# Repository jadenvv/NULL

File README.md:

# NULL: A Development Board for Pentesters
NULL is a ESP32-S3 based PCB board with capabilities of infrared emulation, RFID transceiving, ARP-spoofing on WiFi Networks, and LoRa Puck capabilities. Developed with a mixture of the ESP-IDF development environment 
## What was the motivation for NULL? 
The origins of the development of NULL really came out of the intrigue of the flipper zero. I wanted to create a cheaper alternative to what seemed like an amazing development board for pentesting enthuastist. And, not only did I create a cheaper alternative for myself, but added an additional feature of a LoRA puck boosting the overall usefullness of the board.
## Images of Schematic & Wiring 

4 Layer Board with the layout
<- SIGNAL  ->
<- GND  ->
<- POWER  ->
<- SIGNAL/GND  ->

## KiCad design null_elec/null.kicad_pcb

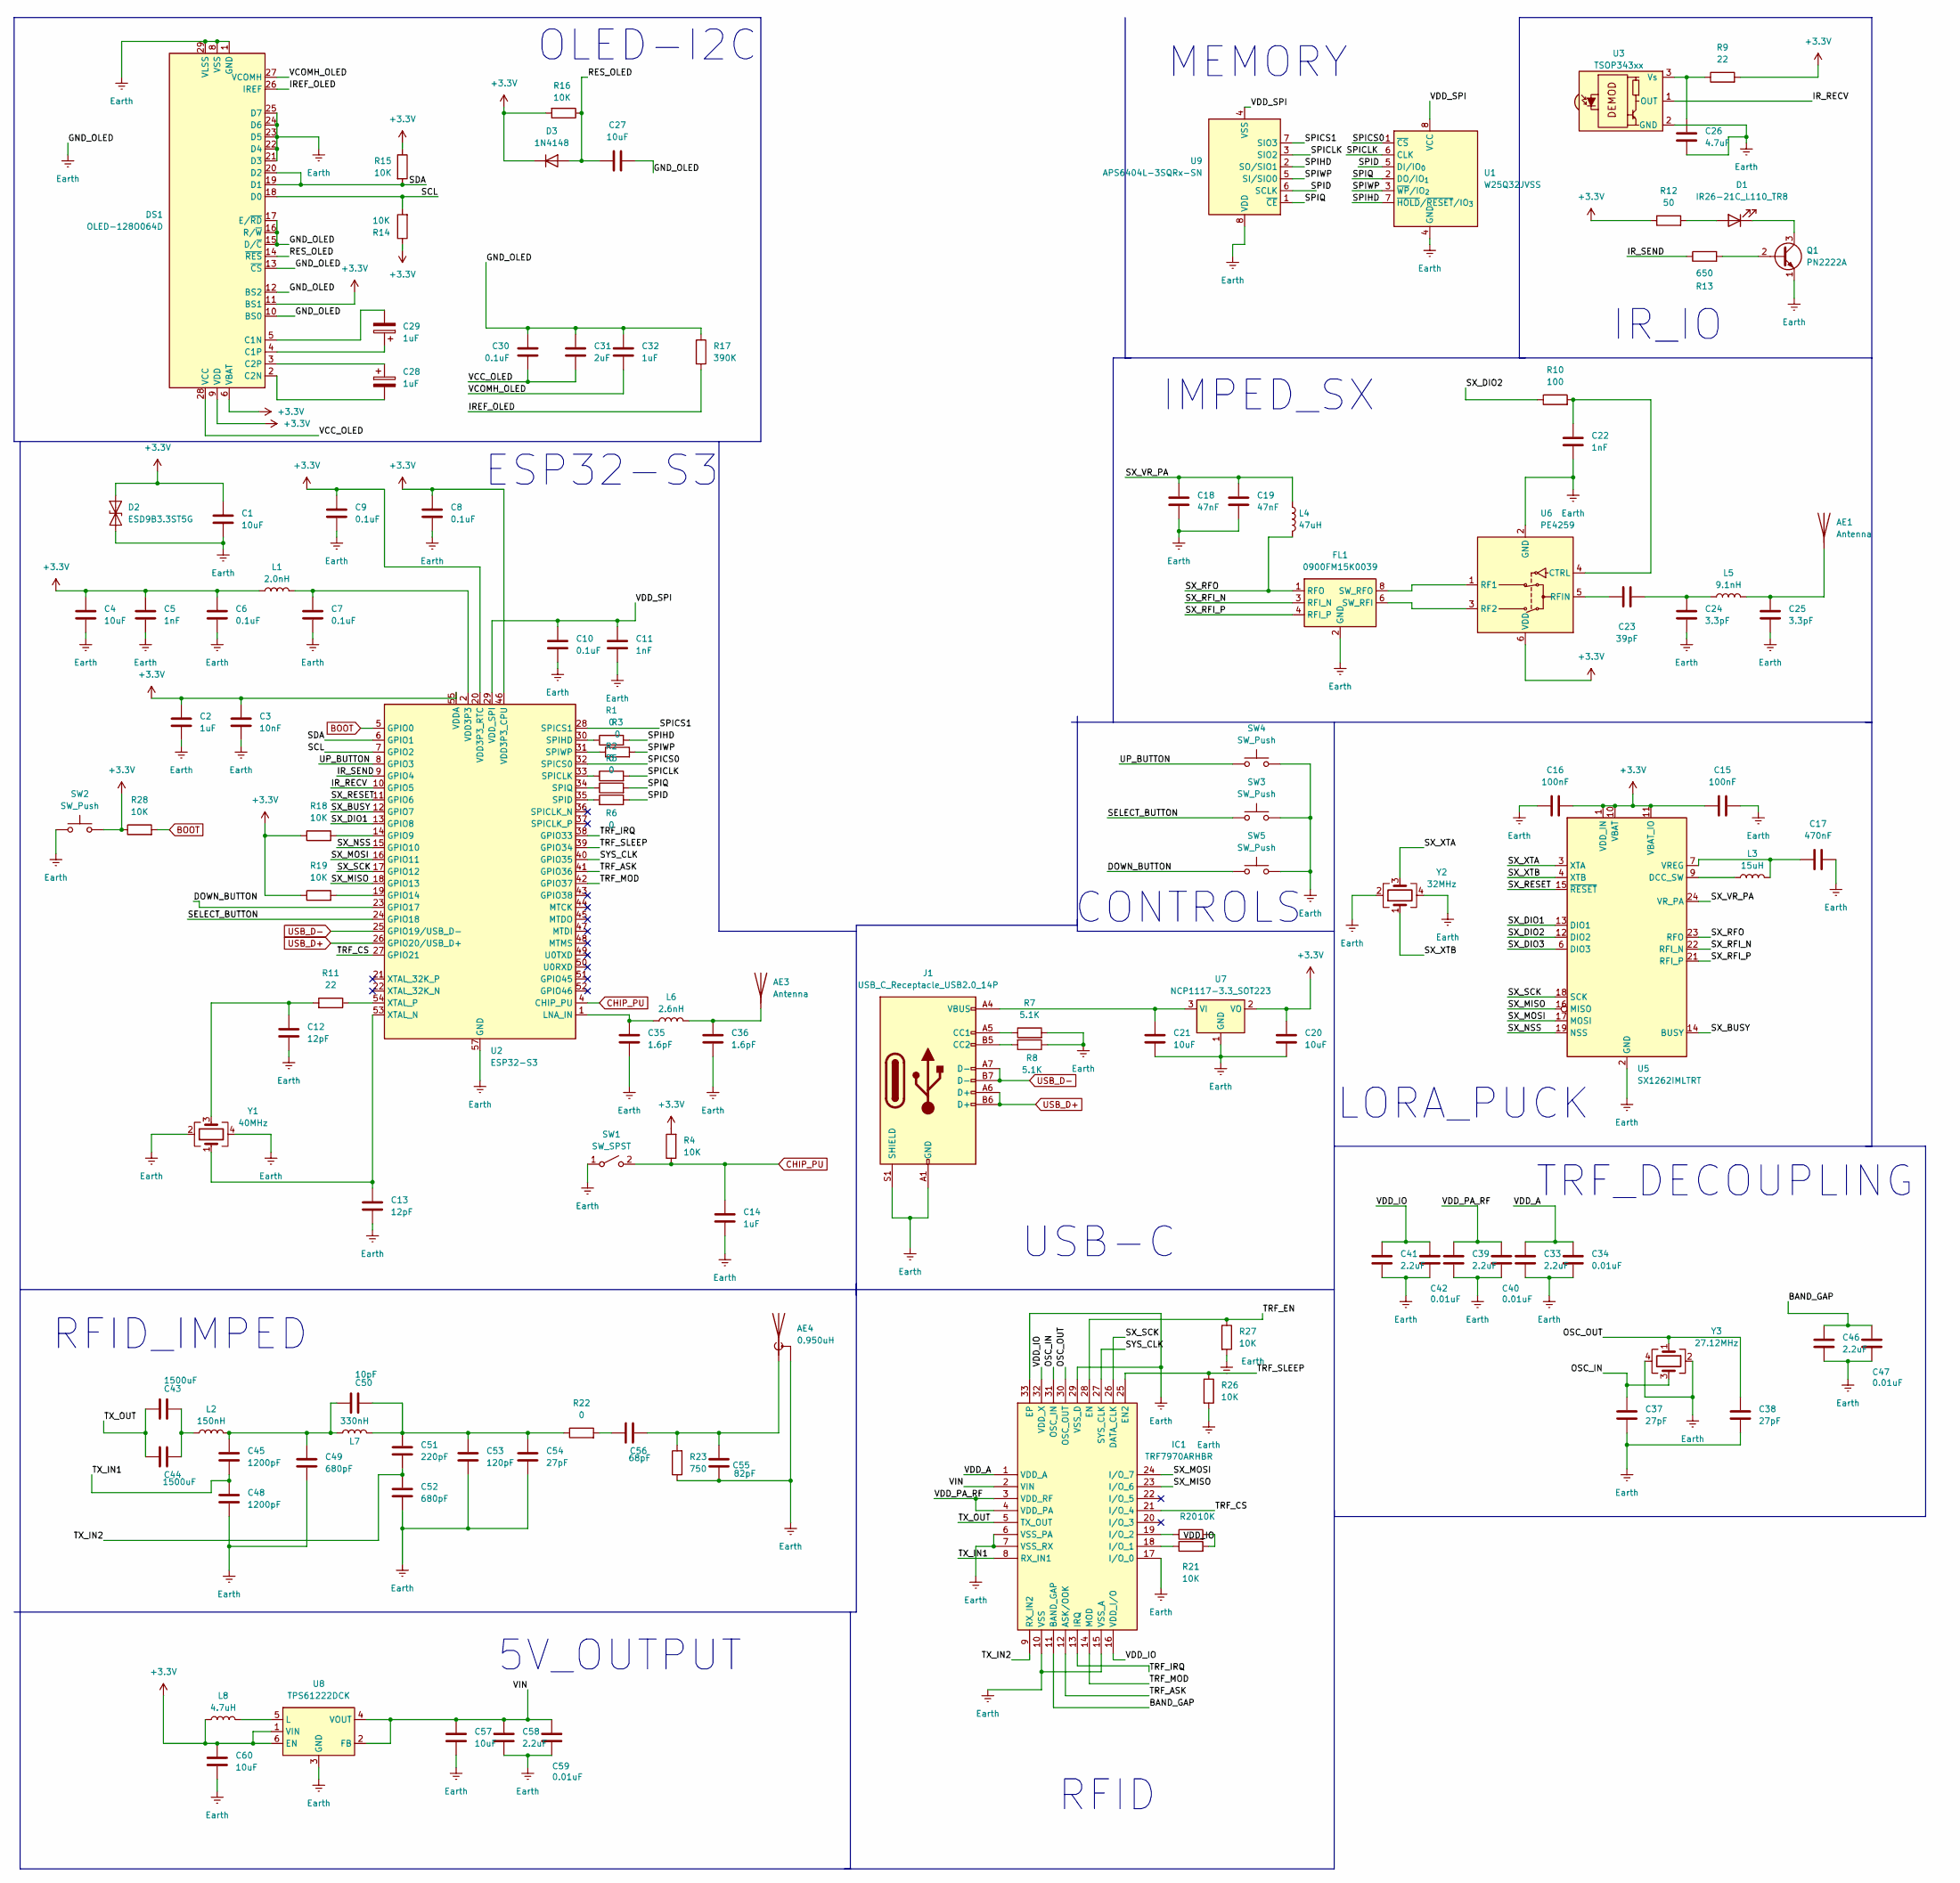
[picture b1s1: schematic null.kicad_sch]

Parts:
AE1: Antenna; PinSocket_1x01_P2.54mm_Vertical
AE3: Antenna; Molex_47948-0001_2.4Ghz
AE4: 0.950uH; Coilcraft_MA5532-AE_RFID
C1, C4, C20, C21, C60: 10uF; C_0805_2012Metric
C2, C14, C28, C29, C32: 1uF; C_0402_1005Metric
C3: 10nF; C_0805_2012Metric
C5, C11, C22: 1nF; C_0402_1005Metric
C6, C7, C8, C9, C10, C30: 0.1uF; C_0402_1005Metric
C12, C13: 12pF; C_0402_1005Metric
C15, C16: 100nF; C_0402_1005Metric
C17: 470nF; C_0402_1005Metric
C18, C19: 47nF; C_0402_1005Metric
C23: 39pF; C_0402_1005Metric
C24, C25: 3.3pF; C_0402_1005Metric
C26: 4.7uF; C_0402_1005Metric
C27, C57: 10uF; C_0402_1005Metric
C31: 2uF; C_0402_1005Metric
C33, C39, C41, C46, C58: 2.2uF; C_0402_1005Metric
C34, C40, C42, C47, C59: 0.01uF; C_0402_1005Metric
C35, C36: 1.6pF; C_0402_1005Metric
C37, C38, C54: 27pF; C_0402_1005Metric
C43, C44: 1500uF; C_0402_1005Metric
C45, C48: 1200pF; C_0402_1005Metric
C49, C52: 680pF; C_0402_1005Metric
C50: 10pF; C_0402_1005Metric
C51: 220pF; C_0402_1005Metric
C53: 120pF; C_0402_1005Metric
C55: 82pF; C_0402_1005Metric
C56: 68pF; C_0402_1005Metric
D1: IR26-21C_L110_TR8; LED_1206_3216Metric
D2: ESD9B3.3ST5G; D_SOD-923
D3: 1N4148; D_DO-35_SOD27_P7.62mm_Horizontal
DS1: OLED-128O064D
FL1: 0900FM15K0039; Balun_Johanson_0900FM15K0039
IC1: TRF7970ARHBR; QFN50P500X500X100-33N-D; Mouser Part Number 595-TRF7970ARHBR
J1: USB_C_Receptacle_USB2.0_14P; USB_C_Receptacle_HCTL_HC-TYPE-C-16P-01A
L1: 2.0nH; L_0402_1005Metric
L2: 150nH; L_0402_1005Metric
L3: 15uH; L_0402_1005Metric
L4: 47uH; L_0402_1005Metric
L5: 9.1nH; L_0402_1005Metric
L6: 2.6nH; L_0402_1005Metric
L7: 330nH; L_0402_1005Metric
L8: 4.7uH; L_0402_1005Metric
Q1: PN2222A; TO-92_Inline
R1, R2, R3, R5, R6, R22: 0; R_0402_1005Metric
R4, R14, R15, R16, R18, R19, R20, R21, R26, R27, R28: 10K; R_0402_1005Metric
R7, R8: 5.1K; R_0402_1005Metric
R9, R11: 22; R_0402_1005Metric
R10: 100; R_0402_1005Metric
R12: 50; R_0402_1005Metric
R13: 650; R_0402_1005Metric
R17: 390K; R_0402_1005Metric
R23: 750; R_0402_1005Metric
SW1: SW_SPST; SW_SPST_SKQG_WithStem
SW2, SW3, SW4, SW5: SW_Push; SW_Tactile_SPST_NO_Straight_CK_PTS636Sx25SMTRLFS
U1: W25Q32JVSS; SOIC-8_5.3x5.3mm_P1.27mm
U2: ESP32-S3; QFN-56-1EP_7x7mm_P0.4mm_EP4x4mm
U3: TSOP343xx; Vishay_MOLD-3Pin
U5: SX1262IMLTRT; QFN-24-1EP_4x4mm_P0.5mm_EP2.6x2.6mm
U6: PE4259; SOT-363_SC-70-6
U7: NCP1117-3.3_SOT223; SOT-223-3_TabPin2
U8: TPS61222DCK; Texas_R-PDSO-G6
U9: APS6404L-3SQRx-SN; SOIC-8_3.9x4.9mm_P1.27mm
Y1: 40MHz; Crystal_SMD_3225-4Pin_3.2x2.5mm
Y2: 32MHz; Crystal_SMD_3225-4Pin_3.2x2.5mm
Y3: 27.12MHz; Crystal_SMD_3225-4Pin_3.2x2.5mm

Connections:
+3.3V: C1.1, C2.1, C3.1, C4.1, C5.1, C6.1, C8.1, C9.1, C15.2, C16.1, C20.1, C60.1, D2.2 (A2), D3.1 (K), DS1.6 (VBAT), DS1.9 (VDD), DS1.11 (BS1), L1.1, L8.1, R4.2, R9.2, R12.1, R14.1, R15.1, R16.2, R18.1, R19.1, R28.1, SW2.1, U2.20 (VDD3P3_RTC), U2.46 (VDD3P3_CPU), U2.55 (VDDA), U2.56 (VDDA), U5.1 (VDD_IN), U5.10 (VBAT), U5.11 (VBAT_IO), U6.6 (VDD), U7.2 (VO), U8.1 (VIN), U8.6 (EN)
/BAND_GAP: C46.1, C47.1, IC1.11 (BAND_GAP)
/DOWN_BUTTON: SW5.1, U2.23 (GPIO17)
/IREF_OLED: DS1.26 (IREF), R17.2
/IR_RECV: U2.10 (GPIO5), U3.1 (OUT)
/IR_SEND: R13.1, U2.9 (GPIO4)
/OSC_IN: C37.1, IC1.31 (OSC_IN), Y3.3
/OSC_OUT: C38.1, IC1.30 (OSC_OUT), Y3.1
/RES_OLED: C27.1, D3.2 (A), DS1.14 (~RES), R16.1
/SCL: DS1.18 (D0), R14.2, U2.7 (GPIO2)
/SDA: DS1.19 (D1), DS1.20 (D2), R15.2, U2.6 (GPIO1)
/SELECT_BUTTON: SW3.2, U2.24 (GPIO18)
/SPICLK: R2.2, U1.6 (CLK), U9.3 (SIO2)
/SPICS0: U1.1 (~CS), U2.32 (SPICS0)
/SPICS1: U2.28 (SPICS1), U9.7 (SIO3)
/SPID: R6.1, U1.5 (DI/IO_{0}), U9.6 (SCLK)
/SPIHD: R1.2, U1.7 (~HOLD/~RESET/IO_{3}), U9.2 (SO/SIO1)
/SPIQ: R5.2, U1.2 (DO/IO_{1}), U9.1 (~CE)
/SPIWP: R3.2, U1.3 (~WP/IO_{2}), U9.5 (SI/SIO0)
/SX_BUSY: U2.12 (GPIO7), U5.14 (BUSY)
/SX_DIO1: U2.13 (GPIO8), U5.13 (DIO1)
/SX_DIO2: R10.1, U5.12 (DIO2)
/SX_DIO3: U5.6 (DIO3)
/SX_MISO: IC1.23 (I/O_6), U2.18 (GPIO13), U5.16 (MISO)
/SX_MOSI: IC1.24 (I/O_7), U2.16 (GPIO11), U5.17 (MOSI)
/SX_NSS: U2.15 (GPIO10), U5.19 (NSS)
/SX_RESET: U2.11 (GPIO6), U5.15 (~RESET)
/SX_RFI_N: FL1.3 (RFI_N), U5.22 (RFI_N)
/SX_RFI_P: FL1.4 (RFI_P), U5.21 (RFI_P)
/SX_RFO: FL1.1 (RFO), L4.2, U5.23 (RFO)
/SX_SCK: IC1.26 (DATA_CLK), U2.17 (GPIO12), U5.18 (SCK)
/SX_VR_PA: C18.1, C19.1, L4.1, U5.24 (VR_PA)
/SX_XTA: U5.3 (XTA), Y2.3
/SX_XTB: U5.4 (XTB), Y2.1
/SYS_CLK: IC1.27 (SYS_CLK), U2.40 (GPIO35)
/TRF_ASK: IC1.12 (ASK/OOK), U2.41 (GPIO36)
/TRF_CS: IC1.21 (I/O_4), U2.27 (GPIO21)
/TRF_EN: IC1.28 (EN), R27.1
/TRF_IRQ: IC1.13 (IRQ), U2.38 (GPIO33)
/TRF_MOD: IC1.14 (MOD), U2.42 (GPIO37)
/TRF_SLEEP: IC1.25 (EN2), R26.1, U2.39 (GPIO34)
/TX_IN1: C45.2, C48.1, IC1.8 (RX_IN1)
/TX_IN2: C51.2, C52.1, IC1.9 (RX_IN2)
/TX_OUT: C43.2, C44.2, IC1.5 (TX_OUT)
/UP_BUTTON: SW4.1, U2.8 (GPIO3)
/VCC_OLED: C30.2, C31.2, DS1.28 (VCC)
/VCOMH_OLED: C32.2, DS1.27 (VCOMH)
/VDD_A: C33.1, C34.1, IC1.1 (VDD_A)
/VDD_IO: C41.1, C42.1, IC1.16 (VDD_I/O), IC1.32 (VDD_X), R20.2, R21.2
/VDD_PA_RF: C39.1, C40.1, IC1.3 (VDD_RF), IC1.4 (VDD_PA)
/VDD_SPI: C10.1, C11.1, U1.8 (VCC), U2.29 (VDD_SPI), U9.4 (VSS)
/VIN: C57.1, C58.1, C59.1, IC1.2 (VIN), U8.2 (FB), U8.4 (VOUT)
BOOT: R28.2, U2.5 (GPIO0)
CHIP_PU: C14.1, R4.1, SW1.2 (B), U2.4 (CHIP_PU)
Earth: AE4.2 (Shield), C1.2, C2.2, C3.2, C4.2, C5.2, C6.2, C7.2, C8.2, C9.2, C10.2, C11.2, C12.2, C13.2, C14.2, C15.1, C16.2, C17.2, C18.2, C19.2, C20.2, C21.2, C22.2, C24.2, C25.2, C26.2, C27.2, C30.1, C31.1, C32.1, C33.2, C34.2, C35.2, C36.2, C37.2, C38.2, C39.2, C40.2, C41.2, C42.2, C46.2, C47.2, C48.2, C49.2, C52.2, C53.2, C54.2, C55.2, C57.2, C58.2, C59.2, C60.2, D2.1 (A1), DS1.1 (GND), DS1.8 (VSS), DS1.10 (BS0), DS1.12 (BS2), DS1.13 (~CS), DS1.15 (D/~C), DS1.16 (R/~W), DS1.17 (E/~RD), DS1.21 (D3), DS1.22 (D4), DS1.23 (D5), DS1.24 (D6), DS1.25 (D7), DS1.29 (VLSS), DS1.30 (GND), FL1.2 (GND), FL1.5 (GND), FL1.7 (GND), FL1.9 (GND), FL1.10 (GND), IC1.6 (VSS_PA), IC1.7 (VSS_RX), IC1.10 (VSS), IC1.15 (VSS_A), IC1.17 (I/O_0), IC1.29 (VSS_D), IC1.33 (EP), J1.A1 (GND), J1.A12 (GND), J1.B1 (GND), J1.B12 (GND), J1.S1 (SHIELD), Q1.1 (E), R7.2, R8.1, R17.1, R23.1, R26.2, R27.2, SW1.1 (A), SW2.2, SW3.1, SW4.2, SW5.2, U1.4 (GND), U2.57 (GND), U3.2 (GND), U5.2 (GND), U5.5 (GND), U5.8 (GND), U5.20 (GND), U5.25 (GND), U6.2 (GND), U7.1 (GND), U8.3 (GND), U9.8 (VDD), Y1.2, Y1.4, Y2.2, Y2.4, Y3.2, Y3.4
unnamed: AE1.1 (A), C25.1, L5.2
unnamed: AE3.1 (A), C36.1, L6.2
unnamed: AE4.1 (A), C55.1, C56.1, R23.2
unnamed: C7.1, L1.2, U2.2 (VDD3P3), U2.3 (VDD3P3)
unnamed: C12.1, R11.2, Y1.3
unnamed: C23.2, C24.1, L5.1
unnamed: C43.1, C44.1, L2.1
unnamed: C45.1, C49.1, C50.2, L2.2, L7.1
unnamed: C50.1, C51.1, C53.1, C54.1, L7.2, R22.1
unnamed: C56.2, R22.2
unnamed: D1.2 (A), R12.2
unnamed: D1.1 (K), Q1.3 (C)
unnamed: C29.2, DS1.5 (C1N)
unnamed: C29.1, DS1.4 (C1P)
unnamed: C28.2, DS1.2 (C2N)
unnamed: C28.1, DS1.3 (C2P)
unnamed: FL1.6 (SW_RFI), U6.3 (RF2)
unnamed: FL1.8 (SW_RFO), U6.1 (RF1)
unnamed: IC1.18 (I/O_1), R21.1
unnamed: IC1.19 (I/O_2), R20.1
unnamed: J1.A5 (CC1), R7.1
unnamed: J1.B5 (CC2), R8.2
unnamed: Q1.2 (B), R13.2
unnamed: R18.2, U2.14 (GPIO9)
unnamed: R19.2, U2.19 (GPIO14)
unnamed: C35.1, L6.1, U2.1 (LNA_IN)
unnamed: R2.1, U2.33 (SPICLK)
unnamed: R6.2, U2.35 (SPID)
unnamed: R1.1, U2.30 (SPIHD)
unnamed: R5.1, U2.34 (SPIQ)
unnamed: R3.1, U2.31 (SPIWP)
unnamed: C13.1, U2.53 (XTAL_N), Y1.1
unnamed: R11.1, U2.54 (XTAL_P)
unnamed: C26.1, R9.1, U3.3 (Vs)
unnamed: L3.1, U5.9 (DCC_SW)
unnamed: C17.1, L3.2, U5.7 (VREG)
unnamed: C22.1, R10.2, U6.4 (CTRL)
unnamed: C23.1, U6.5 (RFIN)
unnamed: C21.1, J1.A4 (VBUS), J1.A9 (VBUS), J1.B4 (VBUS), J1.B9 (VBUS), U7.3 (VI)
unnamed: L8.2, U8.5 (L)
USB_D+: J1.A6 (D+), J1.B6 (D+), U2.26 (GPIO20/USB_D+)
USB_D-: J1.A7 (D-), J1.B7 (D-), U2.25 (GPIO19/USB_D-)

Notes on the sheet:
TRF_DECOUPLING
MEMORY
LORA_PUCK
5V_OUTPUT
CONTROLS
RFID_IMPED
OLED-I2C
RFID
IR_IO
ESP32-S3
IMPED_SX
USB-C

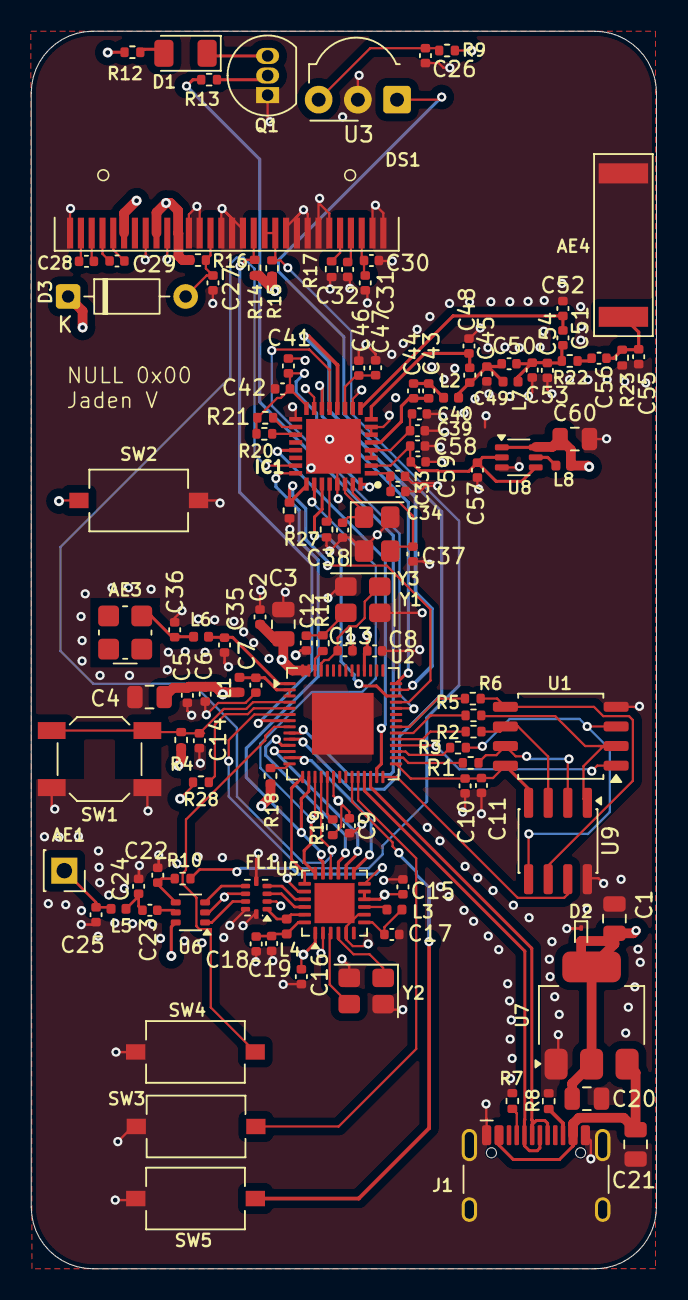
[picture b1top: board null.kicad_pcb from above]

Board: 4 copper layers, 40.5 x 80.2 mm, 121 parts (0 on the bottom side), 96 nets.

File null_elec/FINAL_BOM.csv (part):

JLCPCB BOM Tool - BOM Matching,,,,,,,,,,,,,
BOM name：null-JLCPCB Assembly Order.xlsx,,Download Time：2026-03-06 12:02:31,,"* Our matching results are updated in real-time, but stock and prices may change. 
If it's been over 24 hours, please re-match before placing your order.",,,,,,,,,
PCB Assembled Qty：5,,Est. Total Price：47.1463,,,,,,,,,,,
Your BOM,,,,,,,,Order Information,,,,,
Top Designator,Comment,Footprint,Part # ,Manufacturer,Footprint,Description,Category,JLCPCB Part #,Product link,Lib Type,Qty,Source,Total Price ($)
AE1,Antenna,Connector_PinSocket_2.54mm:PinSocket_1x01_P2.54mm_Vertical,,,,,,,,,,,
AE3,Antenna,RF_Antenna:Molex_47948-0001_2.4Ghz,479480001,MOLEX,"SMD,4x3.2mm","-40℃~+85℃ 100MHz 2.4GHz 2W 3.2mm 3.2mm 3.7dBi 50Ω Patch Antenna SMD,4x3.2mm Antennas ROHS",Antennas,C152351,https://jlcpcb.com/partdetail/MOLEX-479480001/C152351,Extended,2,2 JLCPCB,2.3406
"C1,C4,C20,C21,C60",10uF,Capacitor_SMD:C_0805_2012Metric,GRM21BR61H106KE43L,Murata Electronics,805,10uF 50V X5R ±10% 0805 Multilayer Ceramic Capacitors MLCC - SMD/SMT ROHS,Multilayer Ceramic Capacitors MLCC - SMD/SMT,C440198,,Basic,14,14 JLCPCB,0.9156
"C2,C14,C28,C29,C32",1uF,Capacitor_SMD:C_0402_1005Metric,CL05A105KA5NQNC,Samsung Electro-Mechanics,402,1uF 25V X5R ±10% 0402 Multilayer Ceramic Capacitors MLCC - SMD/SMT ROHS,Multilayer Ceramic Capacitors MLCC - SMD/SMT,C52923,https://jlcpcb.com/partdetail/53938-CL05A105KA5NQNC/C52923,Basic,20,20 JLCPCB,0.066
C3,10nF,Capacitor_SMD:C_0805_2012Metric,CL21B103KBANNNC,Samsung Electro-Mechanics,805,10nF 50V X7R ±10% 0805 Multilayer Ceramic Capacitors MLCC - SMD/SMT ROHS,Multilayer Ceramic Capacitors MLCC - SMD/SMT,C1710,https://jlcpcb.com/partdetail/2062-CL21B103KBANNNC/C1710,Basic,20,20 JLCPCB,0.13
"C5,C11,C22",1nF,Capacitor_SMD:C_0402_1005Metric,0402B102K500NT,FH (Guangdong Fenghua Advanced Tech),402,1nF 50V X7R ±10% 0402 Multilayer Ceramic Capacitors MLCC - SMD/SMT ROHS,Multilayer Ceramic Capacitors MLCC - SMD/SMT,C1523,https://jlcpcb.com/partdetail/1875-0402B102K500NT/C1523,Basic,20,20 JLCPCB,0.024
"C6,C7,C8,C9,C10,C30, C15,C16,C15,C16",0.1uF,Capacitor_SMD:C_0402_1005Metric,CL05B104KO5NNNC,Samsung Electro-Mechanics,402,100nF 16V X7R ±10% 0402 Multilayer Ceramic Capacitors MLCC - SMD/SMT ROHS,Multilayer Ceramic Capacitors MLCC - SMD/SMT,C1525,https://jlcpcb.com/partdetail/1877-CL05B104KO5NNNC/C1525,Basic,26,26 JLCPCB,0.0338
"C12,C13",12pF,Capacitor_SMD:C_0402_1005Metric,0402CG120J500NT,FH (Guangdong Fenghua Advanced Tech),402,12pF 50V C0G ±5% 0402 Multilayer Ceramic Capacitors MLCC - SMD/SMT ROHS,Multilayer Ceramic Capacitors MLCC - SMD/SMT,C1547,https://jlcpcb.com/partdetail/1899-0402CG120J500NT/C1547,Basic,20,20 JLCPCB,0.022
"C17,C18,C19",470nF,Capacitor_SMD:C_0402_1005Metric,CL05A474KP5NNNC,Samsung Electro-Mechanics,402,10V 470nF X5R ±10% 0402 Multilayer Ceramic Capacitors MLCC - SMD/SMT ROHS,Multilayer Ceramic Capacitors MLCC - SMD/SMT,C47339,https://jlcpcb.com/partdetail/48344-CL05A474KP5NNNC/C47339,Extended,20,20 JLCPCB,0.084
C23,39pF,Capacitor_SMD:C_0402_1005Metric,0402CG390J500NT,FH (Guangdong Fenghua Advanced Tech),402,39pF 50V C0G ±5% 0402 Multilayer Ceramic Capacitors MLCC - SMD/SMT ROHS,Multilayer Ceramic Capacitors MLCC - SMD/SMT,C1563,https://jlcpcb.com/partdetail/1915-0402CG390J500NT/C1563,Extended,20,20 JLCPCB,0.024
"C24,C25",3.3pF,Capacitor_SMD:C_0402_1005Metric,0402CG3R3C500NT,FH (Guangdong Fenghua Advanced Tech),402,3.3pF 50V C0G 0402 Multilayer Ceramic Capacitors MLCC - SMD/SMT ROHS,Multilayer Ceramic Capacitors MLCC - SMD/SMT,C1565,https://jlcpcb.com/partdetail/1917-0402CG3R3C500NT/C1565,Extended,20,20 JLCPCB,0.026
C26,4.7uF,Capacitor_SMD:C_0402_1005Metric,CL05A475MP5NRNC,Samsung Electro-Mechanics,402,10V 4.7uF X5R ±20% 0402 Multilayer Ceramic Capacitors MLCC - SMD/SMT ROHS,Multilayer Ceramic Capacitors MLCC - SMD/SMT,C23733,https://jlcpcb.com/partdetail/24469-CL05A475MP5NRNC/C23733,Basic,20,20 JLCPCB,0.1
"C27,C57",10uF,Capacitor_SMD:C_0402_1005Metric,CL05A106MQ5NUNC,Samsung Electro-Mechanics,402,10uF 6.3V X5R ±20% 0402 Multilayer Ceramic Capacitors MLCC - SMD/SMT ROHS,Multilayer Ceramic Capacitors MLCC - SMD/SMT,C15525,https://jlcpcb.com/partdetail/16204-CL05A106MQ5NUNC/C15525,Basic,20,20 JLCPCB,0.11
"C31,C33,C39,C41,C46,C58",2.2uF,Capacitor_SMD:C_0402_1005Metric,GRM155R60J225KE95D,Murata Electronics,402,2.2uF 6.3V X5R ±10% 0402 Multilayer Ceramic Capacitors MLCC - SMD/SMT ROHS,Multilayer Ceramic Capacitors MLCC - SMD/SMT,C76992,https://jlcpcb.com/partdetail/MurataElectronics-GRM155R60J22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,Extended,22,22 JLCPCB,0.176
"C34,C40,C42,C47,C59",0.01uF,Capacitor_SMD:C_0402_1005Metric,CL05B103KB5NNNC,Samsung Electro-Mechanics,402,10nF 50V X7R ±10% 0402 Multilayer Ceramic Capacitors MLCC - SMD/SMT ROHS,Multilayer Ceramic Capacitors MLCC - SMD/SMT,C15195,https://jlcpcb.com/partdetail/15869-CL05B103KB5NNNC/C15195,Basic,20,20 JLCPCB,0.028
"C35,C36",1.6pF,Capacitor_SMD:C_0402_1005Metric,GJM1555C1H1R6WB01D,Murata Electronics,402,1.6pF 50V C0G 0402 Multilayer Ceramic Capacitors MLCC - SMD/SMT ROHS,Multilayer Ceramic Capacitors MLCC - SMD/SMT,C88881,https://jlcpcb.com/partdetail/MurataElectronics-GJM1555C1H1R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,Extended,8,8 JLCPCB,0.464
"C37,C38,C54",27pF,Capacitor_SMD:C_0402_1005Metric,GJM1555C1H270FB01D,Murata Electronics,402,27pF 50V C0G ±1% 0402 Multilayer Ceramic Capacitors MLCC - SMD/SMT ROHS,Multilayer Ceramic Capacitors MLCC - SMD/SMT,C88883,https://jlcpcb.com/partdetail/MurataElectronics-GJM1555C1H27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,Extended,20,20 JLCPCB,0.598
"C43,C44",1500uF,Capacitor_SMD:C_0402_1005Metric,RX1500UF10V90RV0042,KNSCHA,"SMD,D10xL10.2mm","-55℃~+105℃ 10.2mm 10V 10mm 1500uF 2000hrs@105℃ ±20% SMD,D10xL10.2mm Aluminum Electrolytic Capacitors - SMD ROHS",Aluminum Electrolytic Capacitors - SMD,C2887277,https://jlcpcb.com/partdetail/KNSCHA-RX1500UF10V90RV0042/C2887277,Extended,5,5 JLCPCB,1.187
"C45,C48",1200pF,Capacitor_SMD:C_0402_1005Metric,CC0402KRX7R9BB122,YAGEO,402,1.2nF 50V X7R ±10% 0402 Multilayer Ceramic Capacitors MLCC - SMD/SMT ROHS,Multilayer Ceramic Capacitors MLCC - SMD/SMT,C107021,https://jlcpcb.com/partdetail/YAGEO-CC0402KRX7R9BB122/C107021,Extended,20,20 JLCPCB,0.024
"C49,C52",680pF,Capacitor_SMD:C_0402_1005Metric,0402B681K500NT,FH (Guangdong Fenghua Advanced Tech),402,50V 680pF X7R ±10% 0402 Multilayer Ceramic Capacitors MLCC - SMD/SMT ROHS,Multilayer Ceramic Capacitors MLCC - SMD/SMT,C1541,https://jlcpcb.com/partdetail/1893-0402B681K500NT/C1541,Extended,20,20 JLCPCB,0.024
C50,10pF,Capacitor_SMD:C_0402_1005Metric,CL05C100JB5NNNC,Samsung Electro-Mechanics,402,10pF 50V C0G ±5% 0402 Multilayer Ceramic Capacitors MLCC - SMD/SMT ROHS,Multilayer Ceramic Capacitors MLCC - SMD/SMT,C32949,https://jlcpcb.com/partdetail/33914-CL05C100JB5NNNC/C32949,Basic,20,20 JLCPCB,0.09
C51,220pF,Capacitor_SMD:C_0402_1005Metric,0402B221K500NT,FH (Guangdong Fenghua Advanced Tech),402,220pF 50V X7R ±10% 0402 Multilayer Ceramic Capacitors MLCC - SMD/SMT ROHS,Multilayer Ceramic Capacitors MLCC - SMD/SMT,C1530,https://jlcpcb.com/partdetail/1882-0402B221K500NT/C1530,Basic,20,20 JLCPCB,0.024
C53,120pF,Capacitor_SMD:C_0402_1005Metric,0402N121J500CT,Walsin Tech Corp,402,120pF 50V NP0 ±5% 0402 Multilayer Ceramic Capacitors MLCC - SMD/SMT ROHS,Multilayer Ceramic Capacitors MLCC - SMD/SMT,C237176,https://jlcpcb.com/partdetail/Walsin_TechCorp-0402N121J500CT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,Extended,20,20 JLCPCB,0.036
C55,82pF,Capacitor_SMD:C_0402_1005Metric,0402CG820J500NT,FH (Guangdong Fenghua Advanced Tech),402,50V 82pF C0G ±5% 0402 Multilayer Ceramic Capacitors MLCC - SMD/SMT ROHS,Multilayer Ceramic Capacitors MLCC - SMD/SMT,C45501,https://jlcpcb.com/partdetail/46503-0402CG820J500NT/C45501,Extended,20,20 JLCPCB,0.024
C56,68pF,Capacitor_SMD:C_0402_1005Metric,CL05C680JB5NNNC,Samsung Electro-Mechanics,402,50V 68pF C0G ±5% 0402 Multilayer Ceramic Capacitors MLCC - SMD/SMT ROHS,Multilayer Ceramic Capacitors MLCC - SMD/SMT,C14441,https://jlcpcb.com/partdetail/15103-CL05C680JB5NNNC/C14441,Extended,20,20 JLCPCB,0.092
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
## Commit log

2026-01-31 created idf-project
2026-03-05 added electronics
2026-03-08 i2c init of ssd1306
2026-03-08 added wifi, button files; finished i2c oled impl; need to debug code
2026-03-10 finished debugging; need to add interrupt handling for buttons
2026-03-12 working on startup
2026-03-13 working on IR
2026-03-14 created components and added rust to project
2026-03-15 work
2026-03-18 working on wifi_init
2026-03-19 Add README content for NULL development board
    Added introductory information about the NULL development board, its features, and motivation behind its creation.
2026-03-19 working on WIFI
2026-03-20 working on SPI
2026-03-20 Add schematic and wiring images to README
    Added images and descriptions of the schematic and wiring for the NULL development board.
2026-03-22 working on menu abstraction and states
2026-03-24 adding text for lvgl
2026-03-25 finished with menu; just need to debug; got rid of rust
2026-03-26 No Errors and bugs thank God
2026-03-27 working on wifi connection to AP
2026-03-30 i hate spi documentation
2026-03-31 working onRFID SPI
2026-03-31 worked on interface for RFID
2026-03-31 RFID nearly finsihed
2026-03-31 worked on IR
